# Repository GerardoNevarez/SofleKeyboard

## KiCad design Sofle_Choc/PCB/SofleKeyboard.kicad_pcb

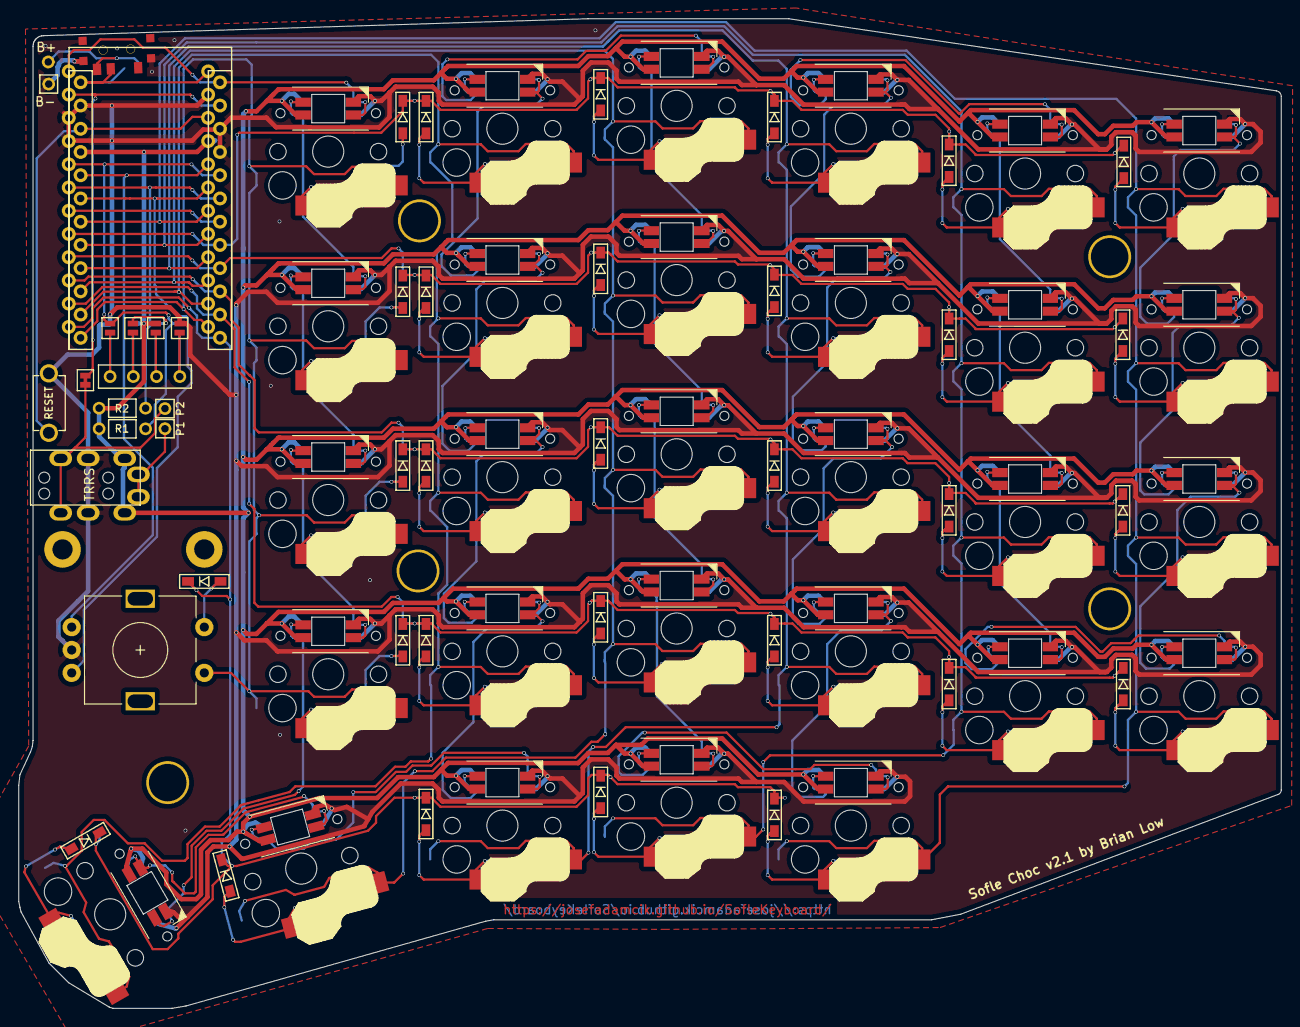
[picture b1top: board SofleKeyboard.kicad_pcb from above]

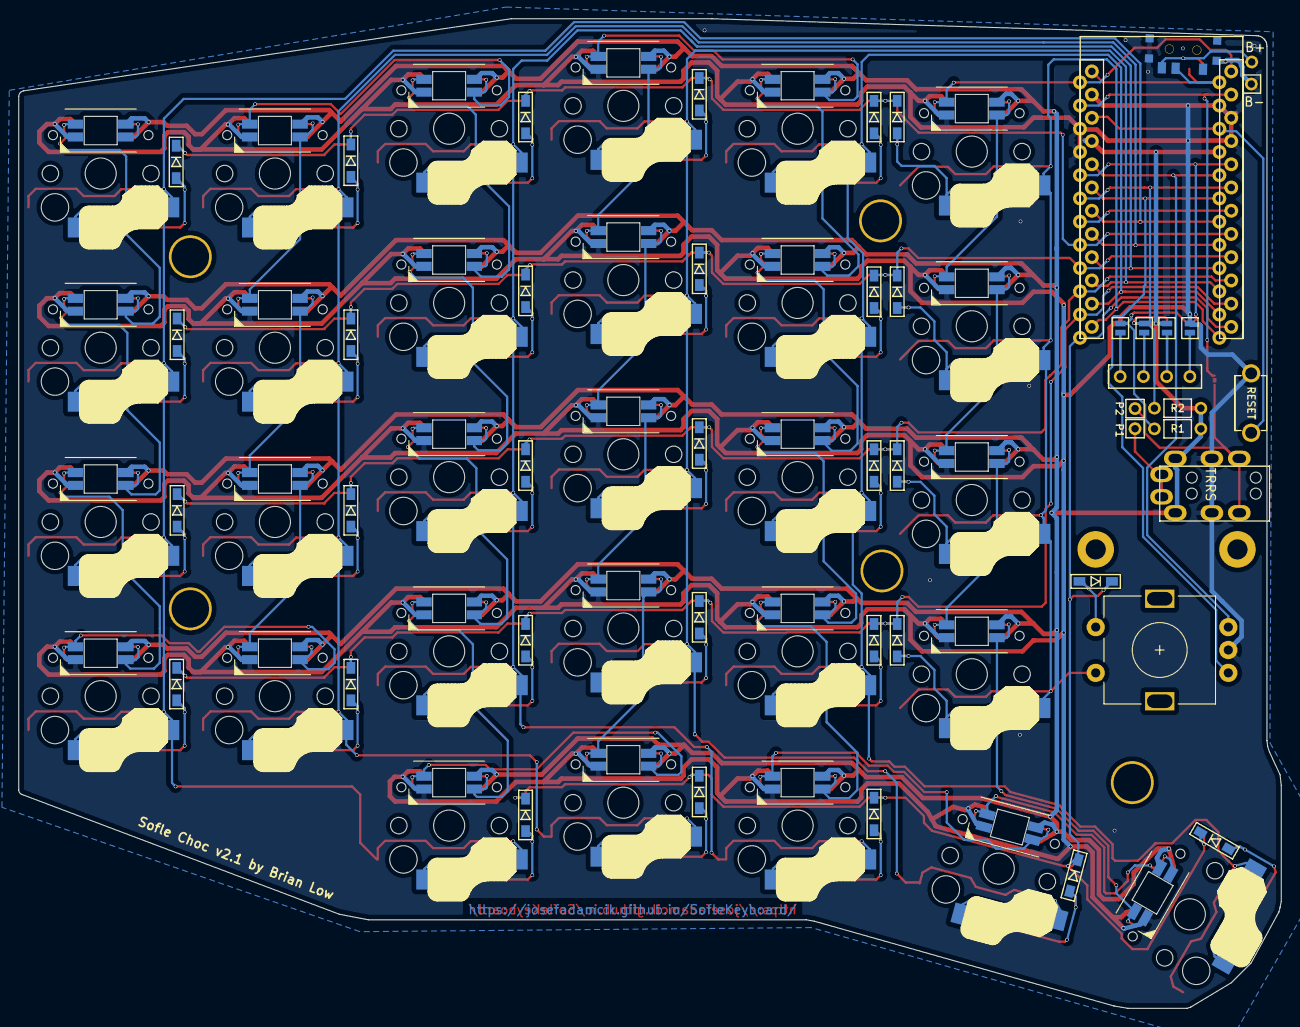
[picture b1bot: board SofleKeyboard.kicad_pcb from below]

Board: 2 copper layers, 138.0 x 108.2 mm, 88 parts (5 on the bottom side), 86 nets.

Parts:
Bat_+1: MountingHole; MountingHole_2.1mm
Bat_-1: MountingHole; MountingHole_2.1mm
D1, D2, D3, D4, D5, D6, D7, D8, D9, D10, D11, D12, D13, D14, D15, D16, D17, D18, D19, D20, D21, D22, D23, D24, D25, D26, D27, D28, D29, D30: D; crkbd-diode
J2: 4PIN; MJ-4PP-9
J3: OLED; OLED_4Pin
JP1, JP2, JP3, JP4, JP5, JP6, JP7, JP8: Jumper_NO_Small; Jumper
P1, P2: i2c_pin; 1pin_conn
Power_SW1: SW_SPDT; SPDT_C128955
Power_SW_R1: SW_SPDT; SPDT_C128955r
R1, R2: R; RESISTOR_mini
RSW1: SW_RST; TACT_SWITCH_TVBP06
SW1, SW2, SW3, SW4, SW5, SW6, SW7, SW8, SW9, SW10, SW11, SW12, SW13, SW14, SW15, SW16, SW17, SW18, SW19, SW20, SW21, SW22, SW23, SW24, SW26, SW27, SW28, SW29, SW30: SW_PUSH_LED; Choc_Hotswap_SK6812MiniE
SW25: Rotary_Encoder_Switch; RotaryEncoder_Alps_EC11E-Switch_Vertical_H20mm-keebio_modif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
TH1, TH2: HOLE; M2_HOLE_PCB
TH3, TH4, TH5, TH6, TH7: HOLE; HOLE_M2_TH
U1: ProMicro
W1: jumper; jumper_data

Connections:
/i2c_c: J2.4, P1.1
/i2c_d: J2.3, P2.1, W1.2
Bat+: Power_SW1.3, Power_SW_R1.3
DATA: U1.2, W1.1
ENCA: SW25.A, U1.20
ENCB: SW25.B, U1.19
GND: J2.2, JP1.2, JP8.2, Power_SW1.0, Power_SW_R1.0, RSW1.1, SW1.3, SW2.3, SW3.3, SW4.3, SW5.3, SW6.3, SW7.3, SW8.3, SW9.3, SW10.3, SW11.3, SW12.3, SW13.3, SW14.3, SW15.3, SW16.3, SW17.3, SW18.3, SW19.3, SW20.3, SW21.3, SW22.3, SW23.3, SW24.3, SW25.C, SW26.3, SW27.3, SW28.3, SW29.3, SW30.3, U1.3, U1.4, U1.23
LED: SW1.4, U1.1
unnamed: D1.2, SW1.5
unnamed: D2.2, SW2.5
unnamed: D3.2, SW3.5
unnamed: D4.2, SW4.5
unnamed: D5.2, SW5.5
unnamed: D6.2, SW6.5
unnamed: D7.2, SW7.5
unnamed: D8.2, SW8.5
unnamed: D9.2, SW9.5
unnamed: D10.2, SW10.5
unnamed: D11.2, SW11.5
unnamed: D12.2, SW12.5
unnamed: D13.2, SW13.5
unnamed: D14.2, SW14.5
unnamed: D15.2, SW15.5
unnamed: D16.2, SW16.5
unnamed: D17.2, SW17.5
unnamed: D18.2, SW18.5
unnamed: D19.2, SW19.5
unnamed: D20.2, SW20.5
unnamed: D21.2, SW21.5
unnamed: D22.2, SW22.5
unnamed: D23.2, SW23.5
unnamed: D24.2, SW24.5
unnamed: D26.2, SW26.5
unnamed: D27.2, SW27.5
unnamed: D28.2, SW28.5
unnamed: D29.2, SW29.5
unnamed: D30.2, SW30.5
unnamed: J3.1, JP4.1, JP8.1
unnamed: J3.2, JP3.1, JP7.1
unnamed: J3.3, JP2.1, JP6.1
unnamed: J3.4, JP1.1, JP5.1
unnamed: SW1.2, SW7.4
unnamed: SW2.2, SW3.4
unnamed: SW2.4, SW8.2
unnamed: SW3.2, SW9.4
unnamed: SW4.2, SW5.4
unnamed: SW4.4, SW10.2
unnamed: SW10.4, SW16.2
unnamed: SW11.2, SW17.4
unnamed: SW5.2, SW11.4
unnamed: SW6.4, SW12.2
unnamed: SW12.4, SW18.2
unnamed: SW13.2, SW19.4
unnamed: SW7.2, SW13.4
unnamed: SW8.4, SW14.2
unnamed: SW14.4, SW20.2
unnamed: SW15.2, SW21.4
unnamed: SW9.2, SW15.4
unnamed: SW16.4, SW22.2
unnamed: SW17.2, SW23.4
unnamed: SW18.4, SW24.2
unnamed: SW19.2, SW26.4
unnamed: SW20.4, SW28.2
unnamed: SW21.2, SW29.4
unnamed: SW22.4, SW30.2
unnamed: SW23.2, SW24.4
unnamed: SW26.2, SW27.4
unnamed: SW27.2, SW28.4
unnamed: SW29.2, SW30.4
RAW: Power_SW1.2, Power_SW_R1.2, U1.24
RESET: RSW1.2, U1.22
SCL: JP3.2, JP6.2, R2.2, U1.6
SDA: JP4.2, JP5.2, R1.2, U1.5
SW25A: SW1.6, SW7.6, SW13.6, SW19.6, SW25.S1, U1.13
SW25B: D25.2, SW25.S2
VCC: J2.1, JP2.2, JP7.2, R1.1, R2.1, SW1.1, SW2.1, SW3.1, SW4.1, SW5.1, SW6.1, SW7.1, SW8.1, SW9.1, SW10.1, SW11.1, SW12.1, SW13.1, SW14.1, SW15.1, SW16.1, SW17.1, SW18.1, SW19.1, SW20.1, SW21.1, SW22.1, SW23.1, SW24.1, SW26.1, SW27.1, SW28.1, SW29.1, SW30.1, U1.21
col0: SW6.6, SW12.6, SW18.6, SW24.6, SW30.6, U1.18
col1: SW5.6, SW11.6, SW17.6, SW23.6, SW29.6, U1.17
col2: SW4.6, SW10.6, SW16.6, SW22.6, SW28.6, U1.16
col3: SW3.6, SW9.6, SW15.6, SW21.6, SW27.6, U1.15
col4: SW2.6, SW8.6, SW14.6, SW20.6, SW26.6, U1.14
row0: D1.1, D2.1, D3.1, D4.1, D5.1, D6.1, U1.8
row1: D7.1, D8.1, D9.1, D10.1, D11.1, D12.1, U1.9
row2: D13.1, D14.1, D15.1, D16.1, D17.1, D18.1, U1.10
row3: D19.1, D20.1, D21.1, D22.1, D23.1, D24.1, U1.11
row4: D25.1, D26.1, D27.1, D28.1, D29.1, D30.1, U1.12

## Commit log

2021-12-24 Add power switch and battery tht pads to Sofle Choc
2021-12-24 Minimum to meet AllPcb freebie size
2021-12-31 PCB Bottom Case
